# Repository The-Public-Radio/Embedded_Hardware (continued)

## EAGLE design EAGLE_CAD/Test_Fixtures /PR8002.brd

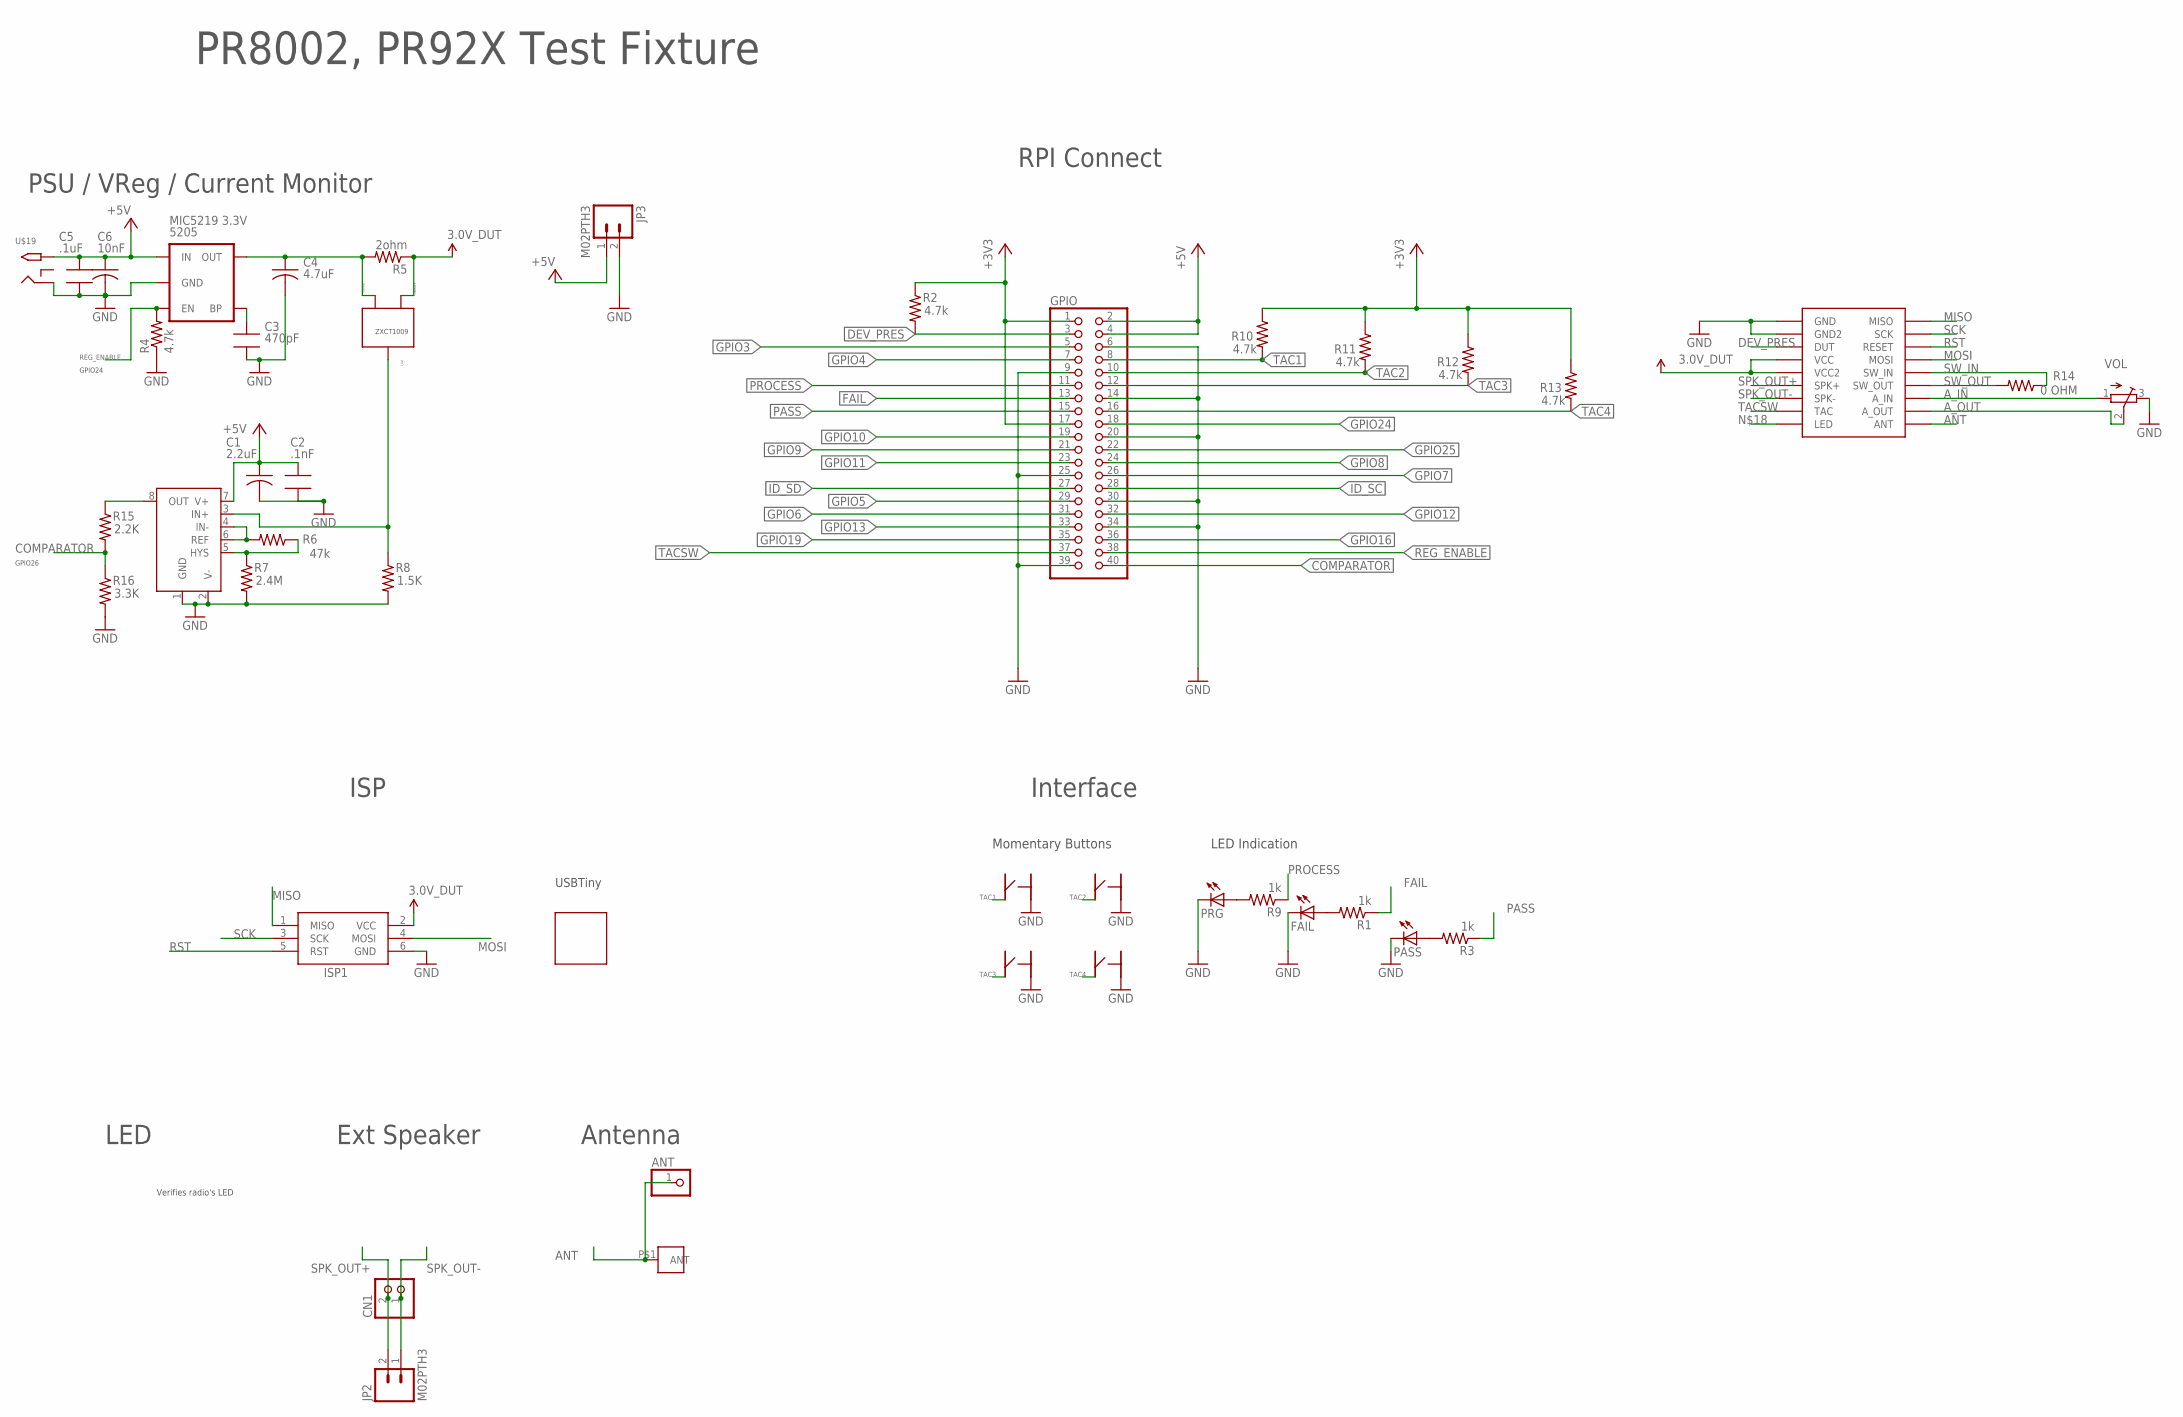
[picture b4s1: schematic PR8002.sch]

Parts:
5205: MIC5219 3.3V; SOT23-5
ANT: PINHD-1X1; 1X01
C1: 2.2uF; C0805
C2: .1nF; 0805_ADAFRUIT
C3: 470pF; 0805_ADAFRUIT
C4: 4.7uF; C0805
C5: .1uF; 0805_ADAFRUIT
C6: 10nF; C0805
CN1: JST_2PIN-SMT-RA; JST-B2B-PH-SM4-TB
FAIL: LEDCHIP-LED0805; CHIP-LED0805
GPIO: PINHD-2X20; 2X20
ISP1: AVRISP-6; AVRISP
J1: M3_SCREW_POST; M3_BOLT_HOLE
JP2, JP3: M02PTH3; 1X02_LONGPADS
PASS: LEDCHIP-LED0805; CHIP-LED0805
PRG: LEDCHIP-LED0805; CHIP-LED0805
R1, R3, R9: 1k; 0805_ADAFRUIT
R2, R4, R10, R11, R12, R13: 4.7k; 0805_ADAFRUIT
R5: 2ohm; 0805_ADAFRUIT
R6: 47k; 0805_ADAFRUIT
R7: 2.4M; 0805_ADAFRUIT
R8: 1.5K; 0805_ADAFRUIT
R14: 0 OHM; 0805_ADAFRUIT
R15: 2.2K; 0805_ADAFRUIT
R16: 3.3K; 0805_ADAFRUIT
TSM931: TSM931; MSOP8
U$19: 2.1MMJACKTHM; PJ-102A
U$20, U$22, U$23, U$24: C&K_PTS645; C&K_PTS645_SMT
U$25: SFUN_POCKETPROGRAMMER
U$26: PR9020_TESTPOINTS
VOL: TRIMPOTTC33X; TC33X
ZXCT: ZXCT1009; SOT23

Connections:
3.3V: ISP1.2 (VCC), R5.1, U$26.P$4 (VCC), U$26.P$5 (VCC2), ZXCT.1 (VSENSE+)
+3V3: GPIO.1, GPIO.17, R2.1, R10.1, R11.1, R12.1, R13.1
+5V: 5205.1 (IN), C1.1, C2.1, C5.1, C6.1, GPIO.2, GPIO.4, JP3.1, TSM931.7 (V+), U$19.TIP
ANT: ANT.1, J1.P$1, U$26.P$18 (ANT)
A_IN: U$26.P$16 (A_IN), VOL.1 (A)
A_OUT: U$26.P$17 (A_OUT), VOL.2 (S)
COMPARATOR: GPIO.40, R15.2, R16.1
DEV_PRES: GPIO.3, R2.2, U$26.P$3 (DUT)
FAIL: GPIO.13, R1.1
GND: 5205.2 (GND), C1.2, C2.2, C3.2, C4.2, C5.2, C6.2, FAIL.C, GPIO.6, GPIO.9, GPIO.14, GPIO.20, GPIO.25, GPIO.30, GPIO.34, GPIO.39, ISP1.6 (GND), JP3.2, PASS.C, PRG.C, R4.1, R7.2, R8.2, R16.2, TSM931.1 (GND), TSM931.2 (V-), U$19.RING, U$20.P$2, U$22.P$2, U$23.P$2, U$24.P$2, U$26.P$1 (GND), U$26.P$2 (GND2), VOL.3 (E)
GPIO3: GPIO.5
GPIO4: GPIO.7
GPIO5: GPIO.29
GPIO6: GPIO.31
GPIO7: GPIO.26
GPIO8: GPIO.24
GPIO9: GPIO.21
GPIO10: GPIO.19
GPIO11: GPIO.23
GPIO12: GPIO.32
GPIO13: GPIO.33
GPIO16: GPIO.36
GPIO19: GPIO.35
GPIO24: GPIO.18
GPIO25: GPIO.22
ID_SC: GPIO.28
ID_SD: GPIO.27
MISO: ISP1.1 (MISO), U$26.P$10 (MISO)
MOSI: ISP1.4 (MOSI), U$26.P$13 (MOSI)
unnamed: R6.2, TSM931.4 (IN-), TSM931.6 (REF)
unnamed: PRG.A, R9.2
unnamed: FAIL.A, R1.2
unnamed: PASS.A, R3.2
unnamed: R15.1, TSM931.8 (OUT)
unnamed: R8.1, TSM931.3 (IN+), ZXCT.3 (IOUT)
unnamed: 5205.4 (BP), C3.1
unnamed: 5205.5 (OUT), C4.1, R5.2, ZXCT.2 (VSENSE-)
unnamed: R6.1, R7.1, TSM931.5 (HYS)
PASS: GPIO.15, R3.1
PROCESS: GPIO.11, R9.1
REG_ENABLE: 5205.3 (EN), GPIO.38, R4.2
RST: ISP1.5 (RST), U$26.P$12 (RESET)
SCK: ISP1.3 (SCK), U$26.P$11 (SCK)
SPK_OUT+: CN1.2 (1), JP2.2, U$26.P$6 (SPK+)
SPK_OUT-: CN1.1 (2), JP2.1, U$26.P$7 (SPK-)
SW_IN: R14.2, U$26.P$14 (SW_IN)
SW_OUT: R14.1, U$26.P$15 (SW_OUT)
TAC1: GPIO.8, R10.2, U$20.P$4
TAC2: GPIO.10, R11.2, U$23.P$4
TAC3: GPIO.12, R12.2, U$22.P$4
TAC4: GPIO.16, R13.2, U$24.P$4
TACSW: GPIO.37, U$26.P$8 (TAC)

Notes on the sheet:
Antenna
Ext Speaker
LED
ISP
PSU / VReg / Current Monitor
RPI Connect
PR8002, PR92X Test Fixture
Verifies radio's LED
Interface
GPIO24
GPIO26
ZXCT1009
USBTiny
Momentary Buttons
LED Indication

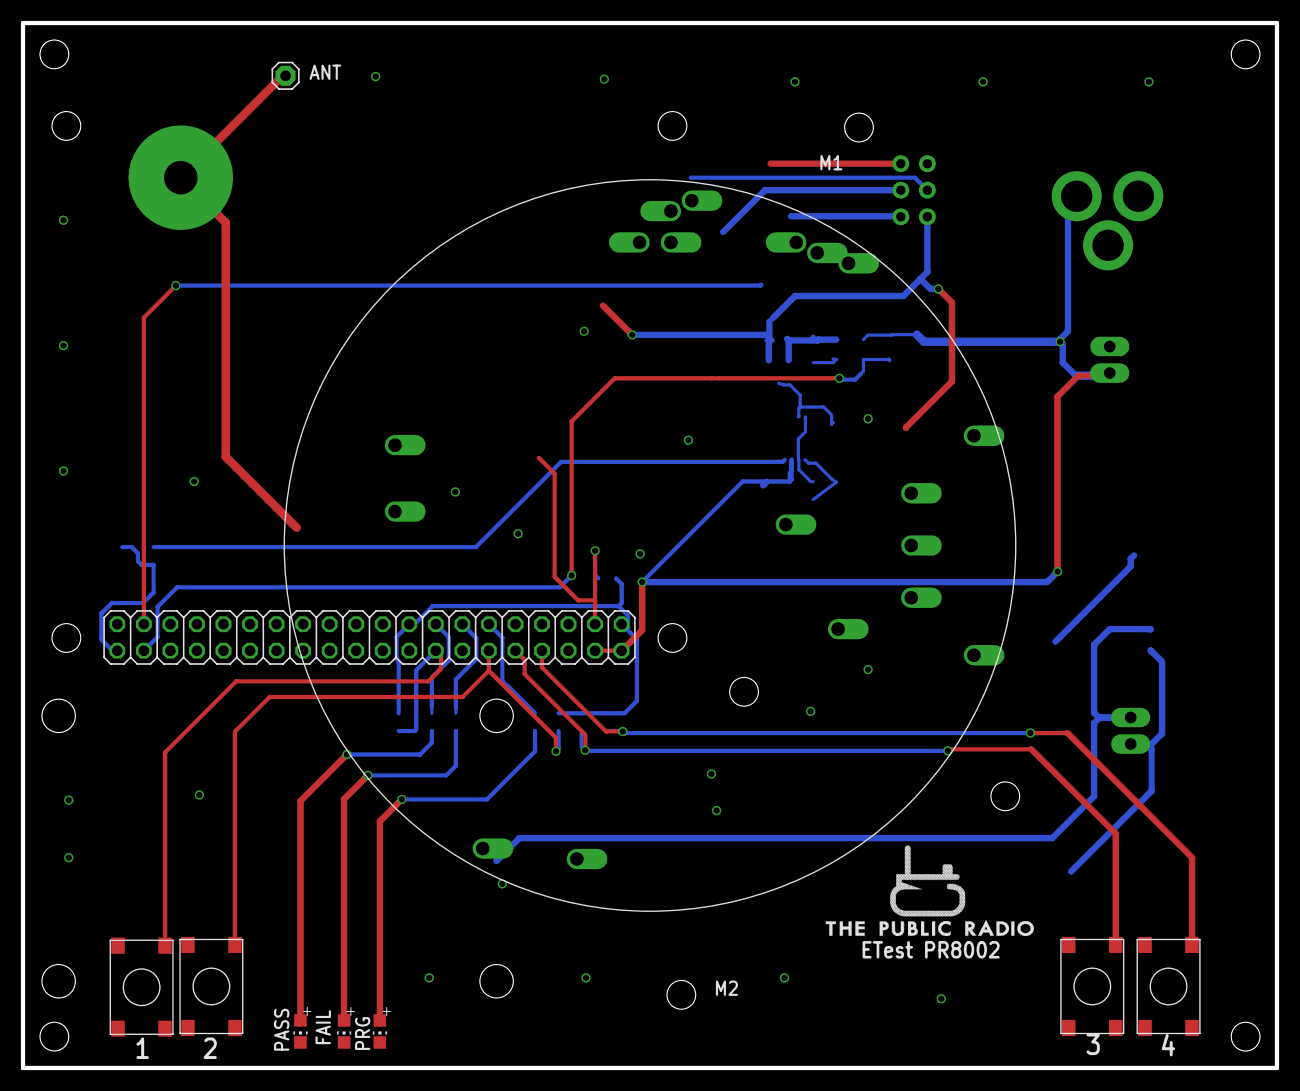
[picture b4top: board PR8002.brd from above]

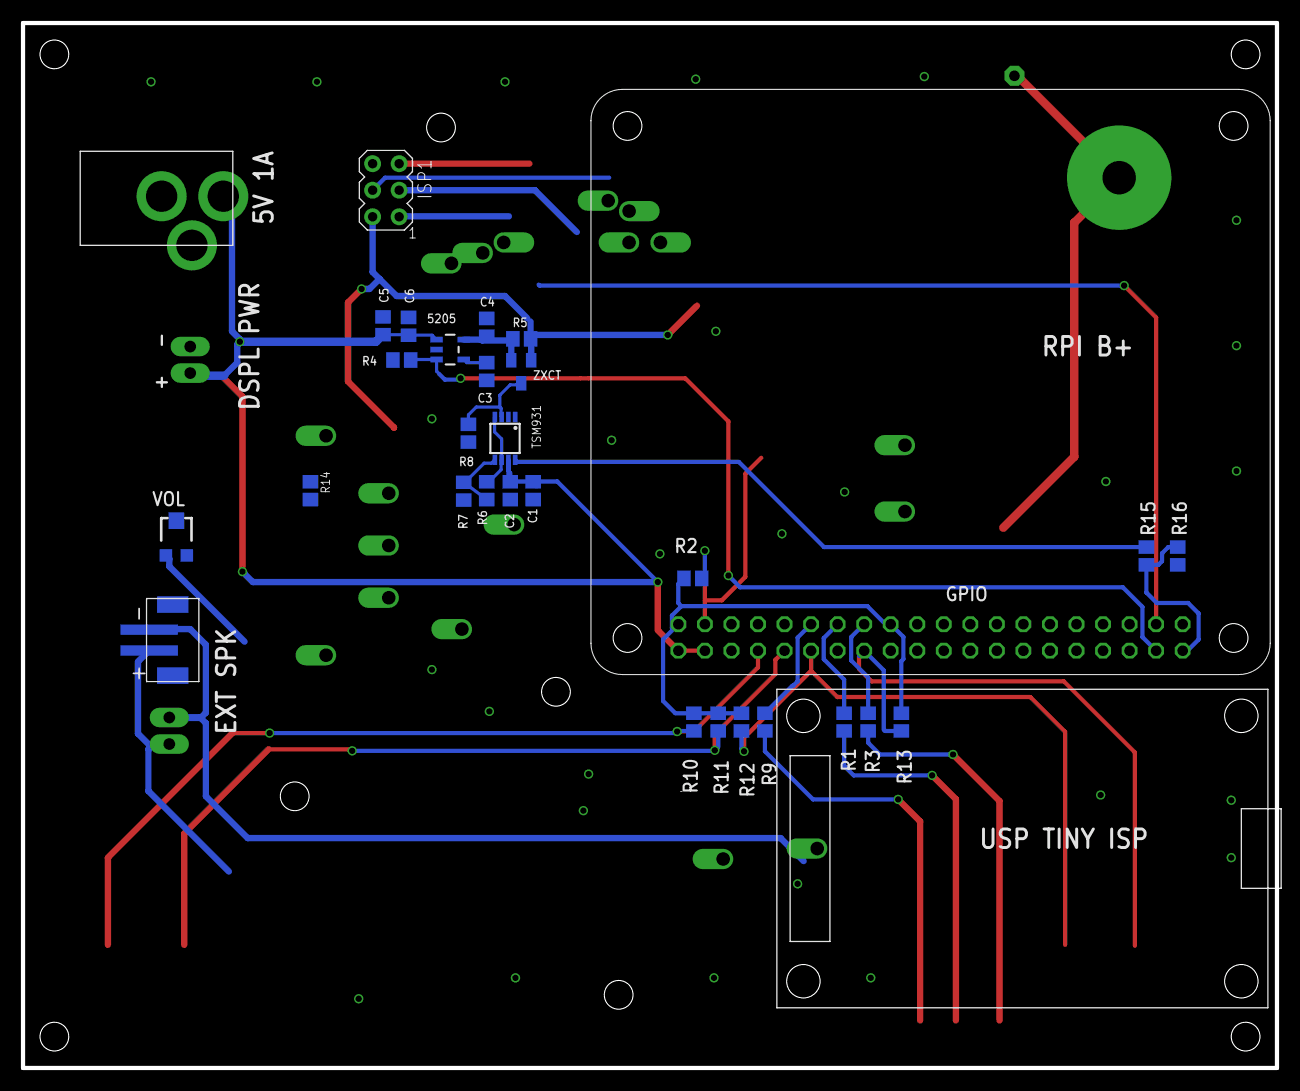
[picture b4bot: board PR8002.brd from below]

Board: 2 copper layers, 120.0 x 100.0 mm, 44 parts (30 on the bottom side), 35 nets.

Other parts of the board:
U$1: PR_LOGO
